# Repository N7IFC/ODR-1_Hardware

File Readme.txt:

This is the hardware repository for the ODR-1 (Open Design Radio - 1) which is a stand-alone "Firmware" defined QRP transceiver.The design goal for the radio is to cover from 1.8MHz (160 meters) up to 50 MHz (6 meters) though it may be able to cover up to 70MHz (4 meters).

The ODR-1 radio consists of the following circuit boards:

1) Display Board
2) Processor Board
3) Oscillator & Mixer Board
4) Amp and tuner board (not released, under design)

Each board hardware revision will have its own directory. When the circuit board layout changes significantly, there is a letter revision. If a minor revision occurs, such as a component value change or a cut and add, then a numeric suffix will be added to the letter revision. this allows older boards to be modified while not impacting the release of new board designs.

All schematic capture and layout is done with stable releases of KiCAD. You are encouraged to support the KiCAD development team as it is an outstanding collection of software.

Hardware - https://github.com/N7IFC/ODR-1_Hardware
Firmware - https://github.com/sylvanwilliams/ODR-1_Firmware

73s!

Bill N7IFC

This work is licensed under the Creative Commons Attribution-ShareAlike 4.0 International License.To view a copy of this license, visit http://creativecommons.org/licenses/by-sa/4.0/ or send a letter to Creative Commons, PO Box 1866, Mountain View, CA 94042, USA.

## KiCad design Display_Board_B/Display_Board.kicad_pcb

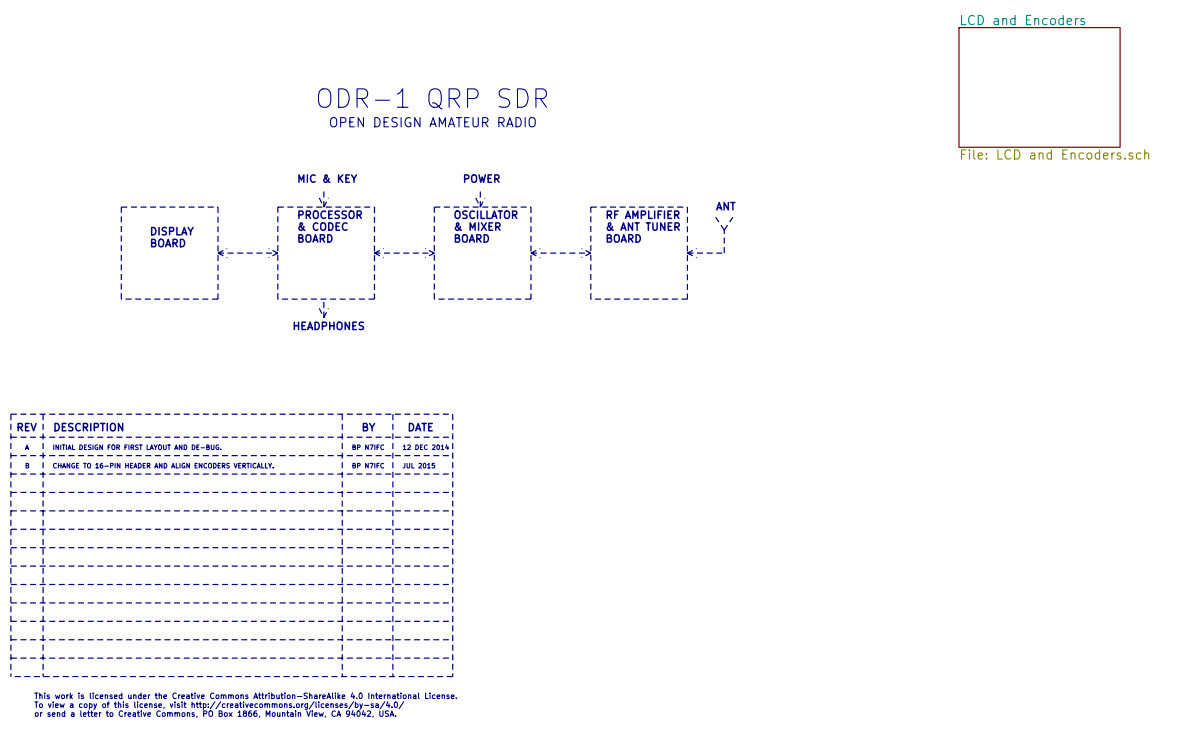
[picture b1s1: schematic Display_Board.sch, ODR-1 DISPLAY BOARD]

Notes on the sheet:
ODR-1 QRP SDR
REV
DESCRIPTION
DATE
INITIAL DESIGN FOR FIRST LAYOUT AND DE-BUG.
BP N7IFC
12 DEC 2014
DISPLAY BOARD
PROCESSOR & CODEC BOARD
OSCILLATOR & MIXER BOARD
RF AMPLIFIER & ANT TUNER BOARD
ANT
MIC & KEY
HEADPHONES
OPEN DESIGN AMATEUR RADIO
POWER
CHANGE TO 16-PIN HEADER AND ALIGN ENCODERS VERTICALLY.
JUL 2015
This work is licensed under the Creative Commons Attribution-ShareAlike 4.0 International License. To view a copy of this license, visit http://creativecommons.org/licenses/by-sa/4.0/ or send a letter to Creative Commons, PO Box 1866, Mountain View, CA 94042, USA.

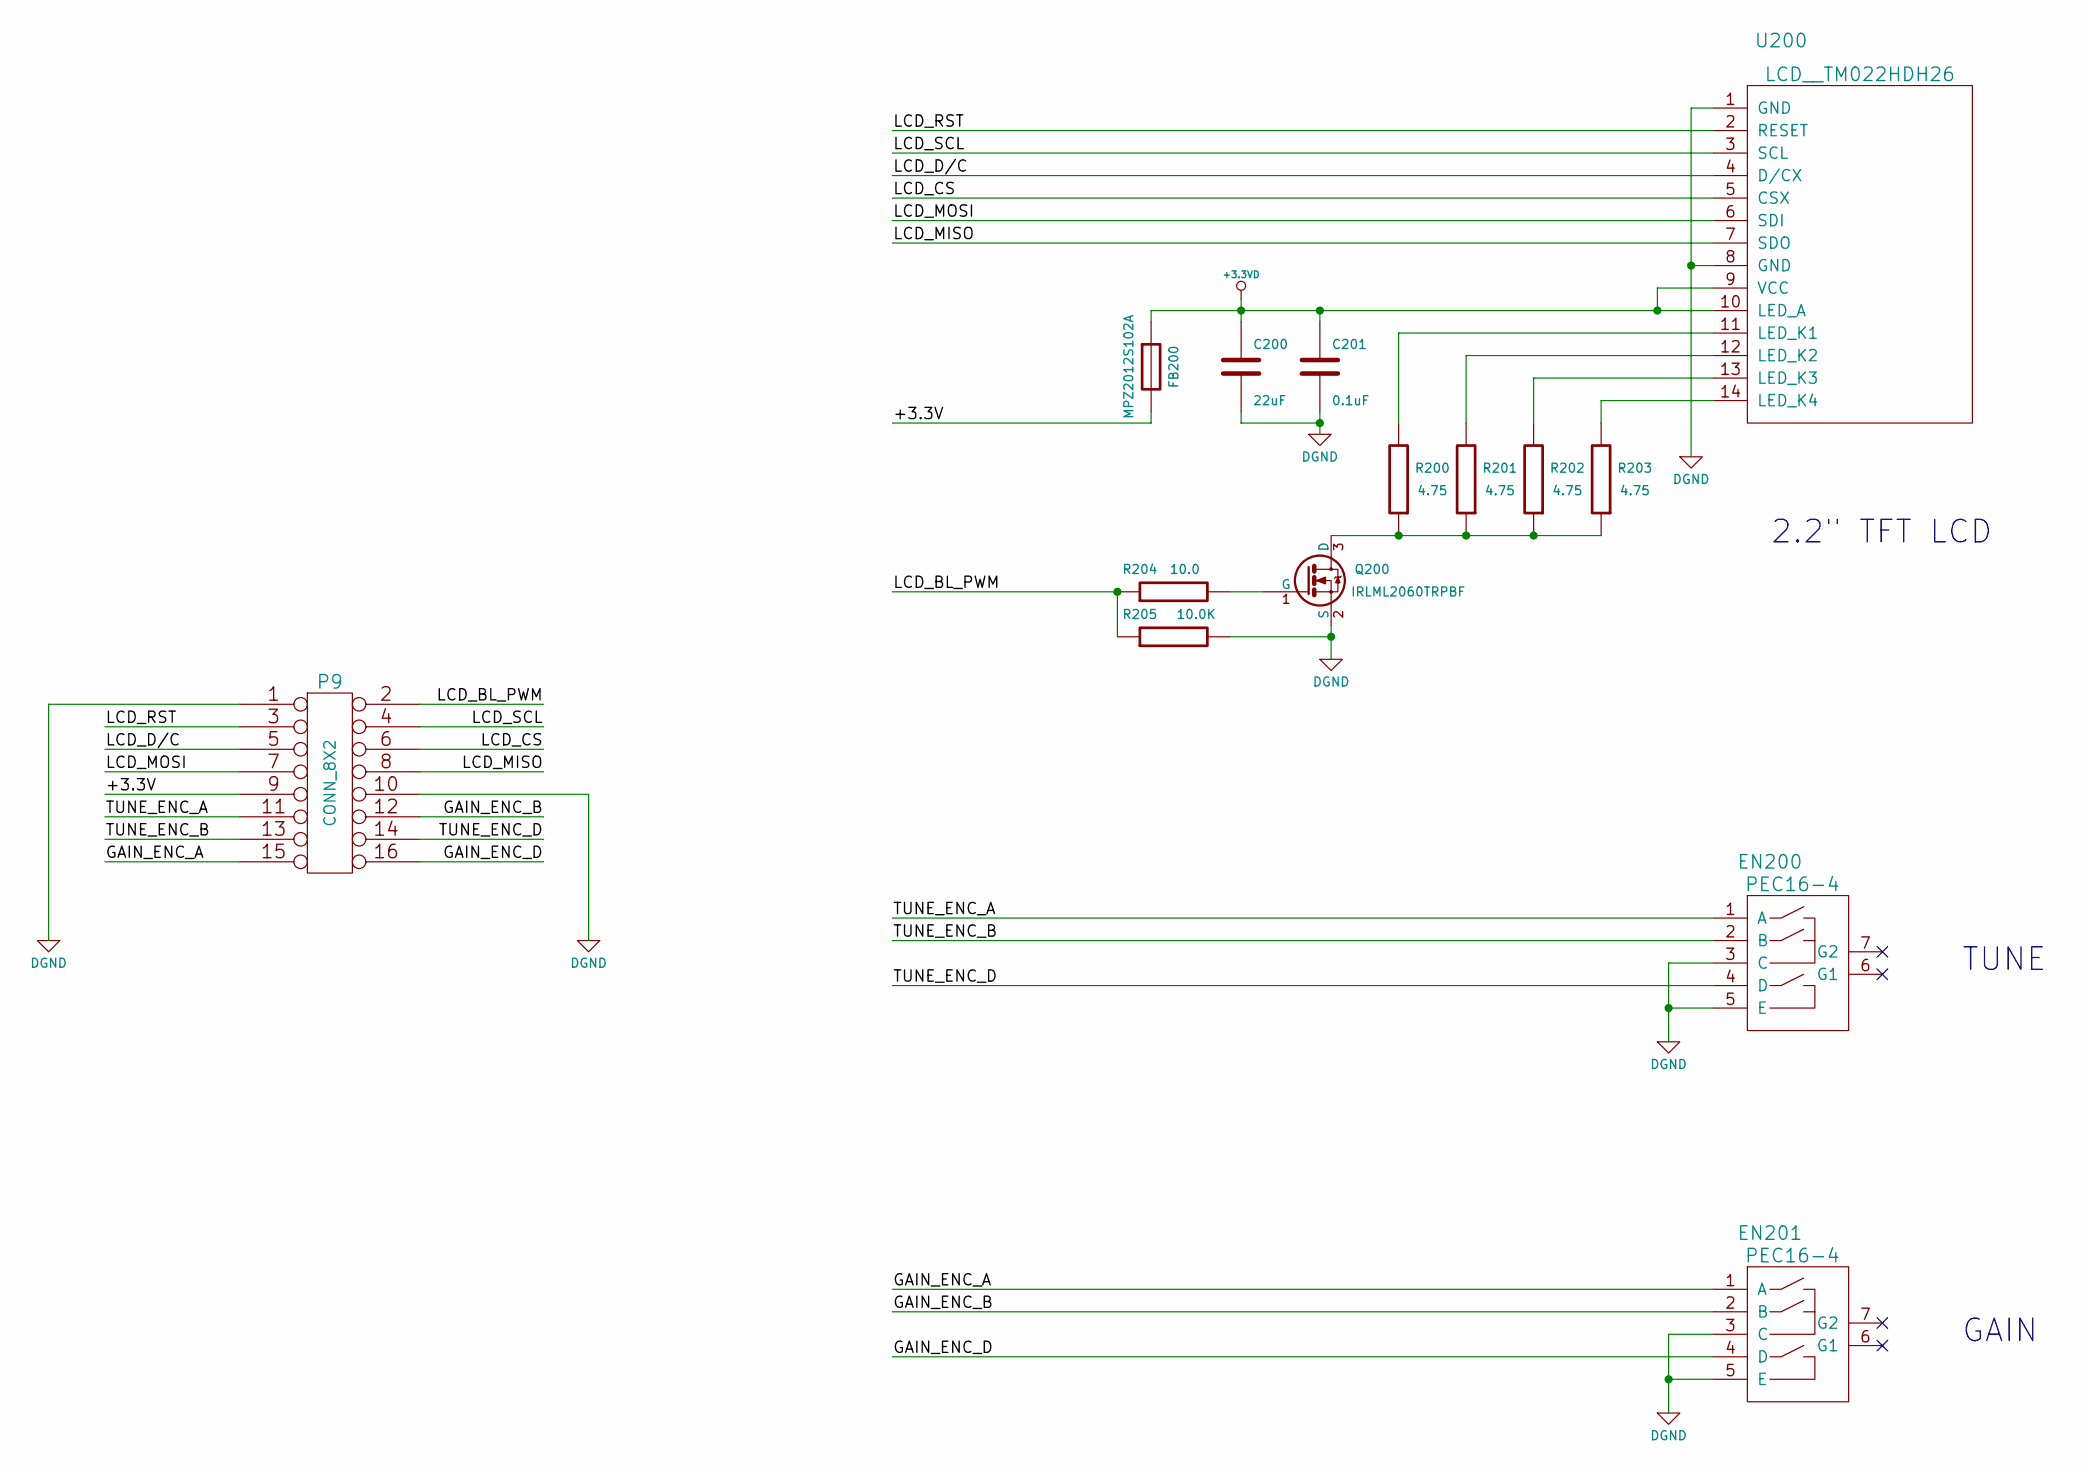
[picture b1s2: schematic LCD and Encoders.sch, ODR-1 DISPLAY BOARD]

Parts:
C200: 22uF; 0805
C201: 0.1uF
EN200, EN201: PEC16-4
FB200: MPZ2012S102A; 0805
P9: CONN_8X2
Q200: IRLML2060TRPBF; SOT-23
R200: 4.75
R201, R202, R203: 4.75; 0805
R204: 10.0; 0805
R205: 10.0K; 0805
U200: LCD__TM022HDH26

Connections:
+3.3VD: C200.1, C201.1, FB200.1, U200.9 (VCC), U200.10 (LED_A)
/LCD and Encoders/+3.3V: FB200.2, P9.9
/LCD and Encoders/GAIN_ENC_A: EN201.1 (A), P9.15
/LCD and Encoders/GAIN_ENC_B: EN201.2 (B), P9.12
/LCD and Encoders/GAIN_ENC_D: EN201.4 (D), P9.16
/LCD and Encoders/LCD_BL_PWM: P9.2, R204.1, R205.1
/LCD and Encoders/LCD_CS: P9.6, U200.5 (CSX)
/LCD and Encoders/LCD_D/C: P9.5, U200.4 (D/CX)
/LCD and Encoders/LCD_MISO: P9.8, U200.7 (SDO)
/LCD and Encoders/LCD_MOSI: P9.7, U200.6 (SDI)
/LCD and Encoders/LCD_RST: P9.3, U200.2 (RESET)
/LCD and Encoders/LCD_SCL: P9.4, U200.3 (SCL)
/LCD and Encoders/TUNE_ENC_A: EN200.1 (A), P9.11
/LCD and Encoders/TUNE_ENC_B: EN200.2 (B), P9.13
/LCD and Encoders/TUNE_ENC_D: EN200.4 (D), P9.14
DGND: C200.2, C201.2, EN200.3 (C), EN200.5 (E), EN201.3 (C), EN201.5 (E), P9.1, P9.10, Q200.2 (S), R205.2, U200.1 (GND), U200.8 (GND)
unnamed: Q200.1 (G), R204.2
unnamed: Q200.3 (D), R200.1, R201.1, R202.1, R203.1
unnamed: R202.2, U200.13 (LED_K3)
unnamed: R200.2, U200.11 (LED_K1)
unnamed: R201.2, U200.12 (LED_K2)
unnamed: R203.2, U200.14 (LED_K4)

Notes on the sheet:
TUNE
GAIN
2.2" TFT LCD

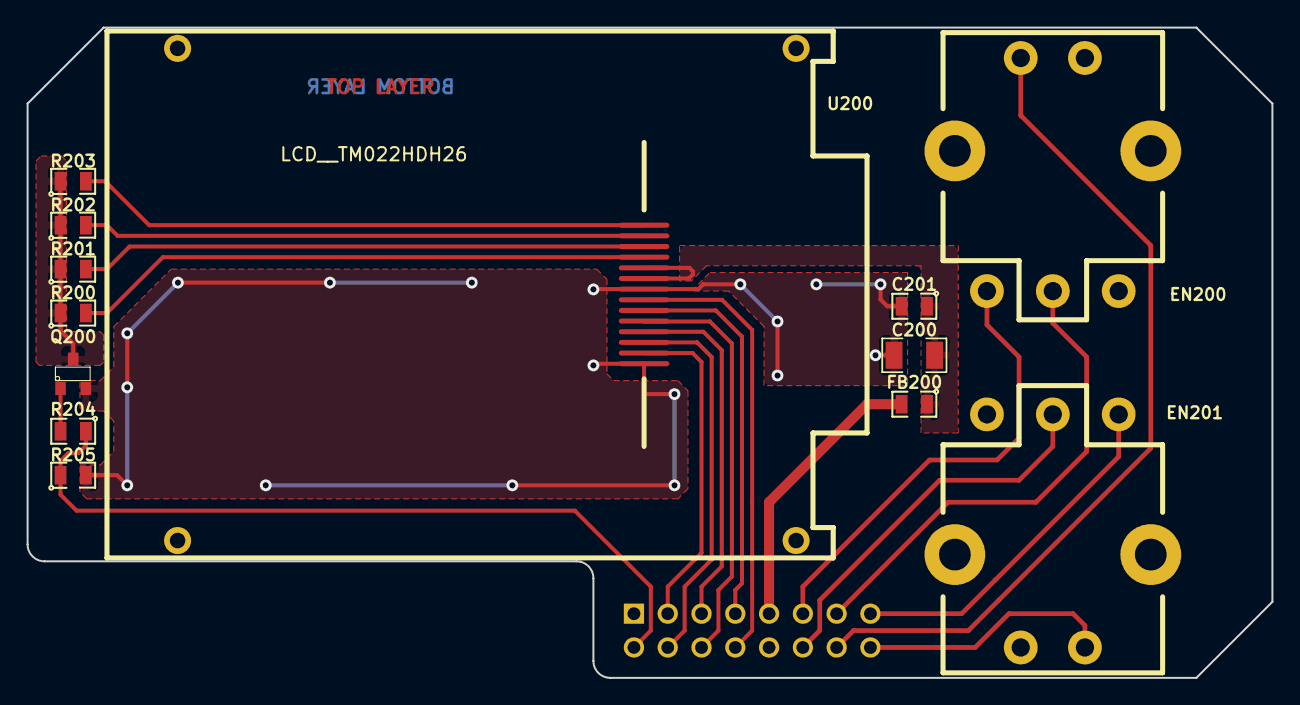
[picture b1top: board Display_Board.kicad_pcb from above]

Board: 2 copper layers, 93.6 x 48.9 mm, 14 parts (1 on the bottom side), 22 nets.

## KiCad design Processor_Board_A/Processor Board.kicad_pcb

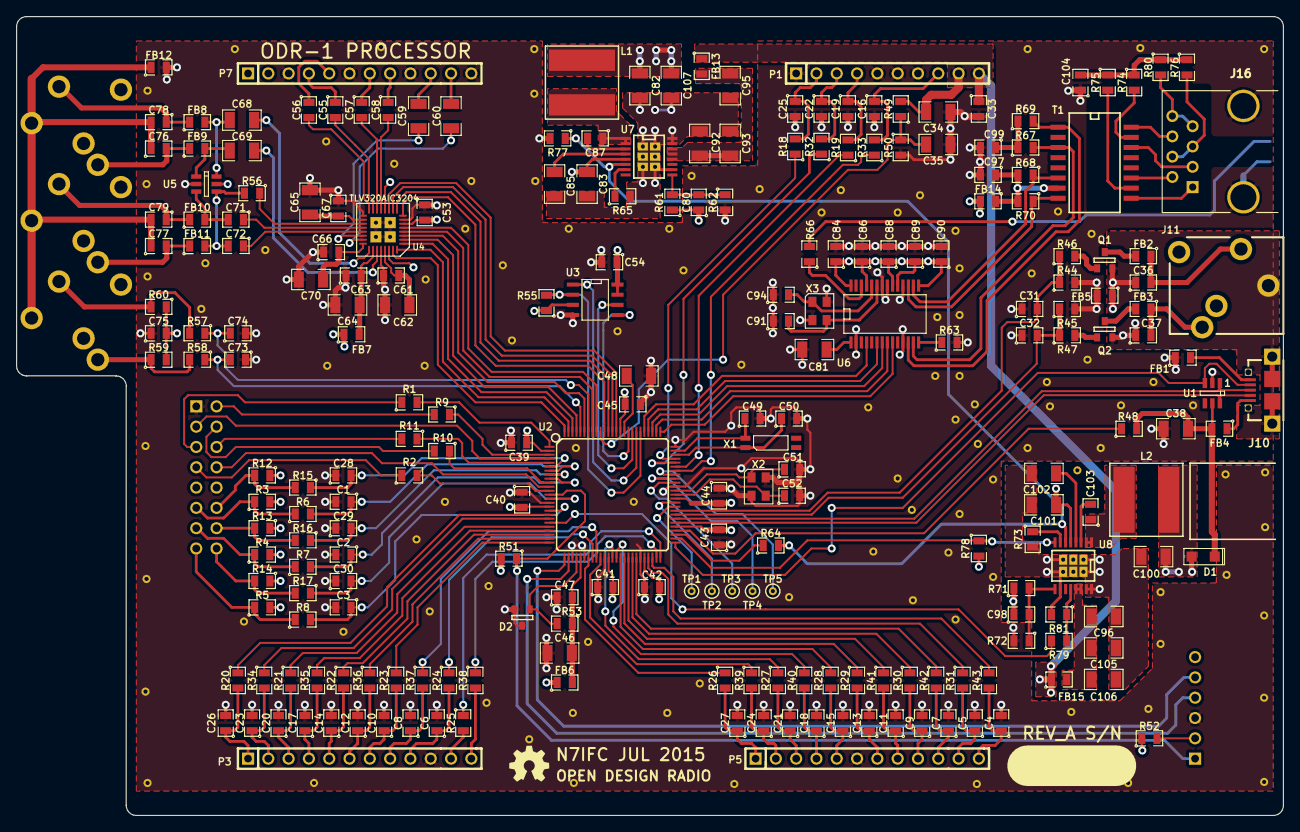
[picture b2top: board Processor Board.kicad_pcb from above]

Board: 4 copper layers, 158.5 x 99.9 mm, 338 parts (0 on the bottom side), 205 nets.

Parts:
C1, C2, C3, C4, C5, C6, C7, C8, C9, C10, C11, C12, C13, C14, C15, C16, C17, C18, C19, C20, C21, C22, C23, C24, C25, C26, C27, C28, C29, C30, C36, C37, C73, C74, C75: 0.01uF; SM0805-1
C31, C32, C76, C77, C78, C79, C104: 1000pF; SM0805-1
C33, C39, C40, C41, C42, C43, C44, C45, C47, C53, C54, C61, C63, C66, C67, C71, C72, C84, C86, C88, C89, C90, C97, C99: 0.1uF; SM0805-1
C34, C38, C81, C83, C93, C95, C101, C105, C106: 4.7uF; SM1206-1
C35, C59, C60, C92, C96: 1uF; SM1206-1
C46, C48, C62, C65: 10uF; SM1206-1
C49, C50, C80, C98: 15pF; SM0805-1
C51, C52, C91, C94: 6pF; SM0805-1
C55, C56, C57, C58: 0.22uF; SM0805-1
C64, C70, C100: 22uF; SM1206-1
C68, C69, C82, C107: 47uF; SM1206-1
C85, C102: 2.2uF; SM1206-1
C87, C103: 0.47uF; SM0805-1
D1: 1A_30V_SCH; SOD123F
D2: LM4040C25; SOT23-1
D3: GRN; SM_LED_RA
FB1, FB2, FB3, FB4, FB5, FB6, FB7, FB12, FB13, FB15: MPZ2012S102A; SM0805-1
FB8, FB9, FB10, FB11, FB14: MMZ2012R102A; SM0805-1
J9: CONN_8X2; HDR_8x2_RA
J10: USB_MICRO_AB
J11, J13, J14, J15: JACK_5P; AUDIO-5
J16: RJ45_LP_UNS; RJ45-8LP
L1: 10uH; SM2233
L2: 22uH; SM2233
P1: M-10; SIL-10-1
P3, P5, P7: M-12; SIL-12-1
P12: CONN_6; SIL-6_RA
Q1, Q2: IRLML2060TRPBF; SOT23-1
R1, R2, R9, R10, R11, R25, R38, R64: 22.1; SM0805-1
R3, R4, R5, R6, R7, R8, R12, R13, R14, R15, R16, R17, R44, R45, R55, R57, R58, R59, R60, R78: 10.0K; SM0805-1
R18, R19, R20, R21, R22, R23, R24, R26, R27, R28, R29, R30, R31, R32, R33, R34, R35, R36, R37, R39, R40, R41, R42, R43, R48, R53: 220; SM0805-1
R46, R47, R77, R79: 1.00K; SM0805-1
R49: 13.7K; SM0805-1
R50: 1.91K; SM0805-1
R51: 4.75K; SM0805-1
R52: 100; SM0805-1
R56: 2.70K; SM0805-1
R61, R71: 1M; SM0805-1
R62: 432K; SM0805-1
R63: 2.32K; SM0805-1
R65, R73: 40.2K; SM0805-1
R66: 270; SM0805-1
R67, R68, R69, R70: 49.9; SM0805-1
R72: 249K; SM0805-1
R74, R75, R76, R80: 75.0; SM0805-1
R81: 100K; SM0805-1
T1: TRANSFO_ETHER; XFMR_ETH16
TP1, TP2, TP3, TP4, TP5: TP_1; TP_TH
U1, U5: TVS_ARRAY_4CH; SOT23-6L
U2: DSPIC33EP512MU810-I/PF (14mm); TQFP_100_14MM
U3: M95256; SO8N-1
U4: TLV320AIC3204; VQFN32
U6: ENC28J60-I/SS; SSOP28-1
U7: LM43601; PWRPAD16
U8: LM43600; PWRPAD16
X1: 32.768 KHz; CRYSTAL_4L
X2: 12.000 MHz; CRYSTAL_4
X3: 25MHz; CRYSTAL_4
x: x; ViaGND40
x#2, x#3, x#4, x#5, x#6, x#7, x#8, x#9, x#10, x#11, x#12, x#13, x#14, x#15, x#16, x#17, x#18, x#19, x#20, x#21, x#22, x#23, x#24, x#25, x#26, x#27, x#28, x#29, x#30, x#31, x#32, x#33, x#34, x#35, x#36, x#37, x#38, x#39, x#40, x#41, x#42, x#43, x#44, x#45, x#46, x#47, x#48, x#49, x#50, x#51, x#52, x#53, x#54, x#55, x#56, x#57, x#58, x#59, x#60, x#61, x#62, x#63, x#64, x#65, x#66, x#67, x#68, x#69, x#70, x#71, x#72, x#73, x#74, x#75, x#76, x#77, x#78, x#79, x#80, x#81, x#82, x#83, x#84, x#85, x#86, x#87, x#88, x#89, x#90, x#91, x#92, x#93, x#94, x#95, x#96, x#97, x#98, x#99, x#100: x; ViaGND40

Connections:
12V_EN: R33.1, U2.69
+3.3VD: C39.2, C40.2, C41.2, C42.2, C43.2, C44.2, C45.2, C53.2, C54.1, C75.2, C80.1, C82.1, C83.1, C84.1, C86.1, C88.1, C89.1, C90.1, C107.1, FB6.1, FB7.1, FB14.2, J9.9, L1.1, R3.2, R4.2, R5.2, R12.1, R13.1, R14.1, R51.2, R52.1, R55.1, R59.2, R60.1, R61.1, R78.2, U2.2, U2.16, U2.37, U2.46, U2.55, U2.62, U2.86, U3.3, U3.7, U3.8, U4.6, U4.12, U4.30, U5.5, U6.15, U6.19, U6.20, U6.25, U6.28, U7.5
+BATT: C33.1, C34.1, FB13.1, FB15.1, P1.9, P1.10, R49.2
/Codec/RX_I+: C55.1, P7.4
/Codec/RX_I-: C56.1, P7.5
/Codec/RX_Q+: C57.1, P7.7
/Codec/RX_Q-: C58.1, P7.8
/Codec/TX_I: C59.1, P7.10
/Codec/TX_Q: C60.1, P7.11
/Processor//MCLR: P12.1, R51.1, U2.13
/Processor/ICSPCLK: P12.5, U2.26
/Processor/ICSPDAT: P12.4, U2.27
AMP-BD01: R32.1, U2.71
AMP-BD02: R19.1, U2.70
AMP-BD03: R34.1, U2.19
AMP-BD04: R21.1, U2.21
AMP-BD05: R35.1, U2.22
AMP-BD06: R22.1, U2.23
AMP-BD07: R36.1, U2.24
AMP-BD08: R23.1, U2.25
AMP-BD09: R37.1, U2.34
AMP-BD10: R24.1, U2.33
AMP-BD11: R26.1, U2.32
AMP-BD12: R39.1, U2.35
AMP-BD13: R27.1, U2.38
AMP-BD14: R40.1, U2.39
AMP-BD15: R28.1, U2.40
ATT_S0: R41.1, U2.42
ATT_S1: R29.1, U2.41
AUX_OUT: C31.2, R44.1, R46.1, U2.59
BATT_V: C35.1, R49.1, R50.1, U2.91
BPF_CS0: R30.1, U2.43
BPF_CS1: R43.1, U2.48
BPF_S0: R31.1, U2.47
BPF_S1: R42.1, U2.44
CODEC_INT1: U2.99, U4.32
CODEC_RST: U2.100, U4.31
COFS-WCLK: U2.95, U4.3
CSCK-BCLK: U2.97, U4.2
CSDI-DOUT: U2.92, U4.5
CSDO-DIN: U2.93, U4.4
GAIN_ENC_A: C3.1, R8.2, U2.17
GAIN_ENC_B: C28.2, R15.1, U2.6
GAIN_ENC_D: C30.2, R17.1, U2.14
GND: C1.2, C2.2, C3.2, C4.2, C5.2, C6.2, C7.2, C8.2, C9.2, C10.2, C11.2, C12.2, C13.2, C14.2, C15.2, C16.2, C17.2, C18.2, C19.2, C20.2, C21.2, C22.2, C23.2, C24.2, C25.2, C26.2, C27.2, C28.1, C29.1, C30.1, C31.1, C32.1, C33.2, C34.2, C35.2, C38.1, C39.1, C40.1, C41.1, C42.1, C43.1, C44.1, C45.1, C46.1, C47.1, C48.1, C49.2, C50.2, C51.2, C52.2, C53.1, C54.2, C61.1, C62.1, C63.1, C64.1, C65.1, C66.1, C67.1, C70.1, C73.1, C74.2, C75.1, C81.2, C82.2, C83.2, C84.2, C85.2, C86.2, C88.2, C89.2, C90.2, C91.1, C92.2, C93.2, C94.1, C95.2, C96.2, C97.2, C99.2, C100.2, C101.2, C102.2, C104.1, C105.2, C106.2, C107.2, D2.2, D2.3, D3.2, FB1.1, FB5.2, FB12.2, J9.1, J9.10, J16.9, J16.10, P1.1, P1.5, P1.6, P1.7, P3.10, P5.6, P7.3, P7.6, P7.9, P7.12, P12.3, R44.2, R45.2, R50.2, R62.2, R63.2, R65.2, R72.2, R73.2, R77.2, R81.2, U1.2, U2.15, U2.28, U2.31, U2.36, U2.45, U2.65, U2.75, U3.4, U4.7, U4.17, U4.28, U4.33, U5.2, U6.2, U6.11, U6.18, U6.21, U6.22, U7.10, U7.15, U7.16, U7.17, U8.10, U8.15, U8.16, U8.17, X2.2, X2.4, X3.2, X3.4, x.1, x#2.1, x#3.1, x#4.1, x#5.1, x#6.1, x#7.1, x#8.1, x#9.1, x#10.1, x#11.1, x#12.1, x#13.1, x#14.1, x#15.1, x#16.1, x#17.1, x#18.1, x#19.1, x#20.1, x#21.1, x#22.1, x#23.1, x#24.1, x#25.1, x#26.1, x#27.1, x#28.1, x#29.1, x#30.1, x#31.1, x#32.1, x#33.1, x#34.1, x#35.1, x#36.1, x#37.1, x#38.1, x#39.1, x#40.1, x#41.1, x#42.1, x#43.1, x#44.1, x#45.1, x#46.1, x#47.1, x#48.1, x#49.1, x#50.1, x#51.1, x#52.1, x#53.1, x#54.1, x#55.1, x#56.1, x#57.1, x#58.1, x#59.1, x#60.1, x#61.1, x#62.1, x#63.1, x#64.1, x#65.1, x#66.1, x#67.1, x#68.1, x#69.1, x#70.1, x#71.1, x#72.1, x#73.1, x#74.1, x#75.1, x#76.1, x#77.1, x#78.1, x#79.1, x#80.1, x#81.1, x#82.1, x#83.1, x#84.1, x#85.1, x#86.1, x#87.1, x#88.1, x#89.1, x#90.1, x#91.1, x#92.1, x#93.1, x#94.1, x#95.1, x#96.1, x#97.1, x#98.1, x#99.1, x#100.1
INT3: U2.80, U6.4
KEY_DOT: C74.1, R57.1, U2.94
KEY_DSH: C73.2, R58.1, U2.96
LCD_BL_PWM: R9.1, U2.3
LCD_CS: R11.1, U2.5
LCD_D-C: R1.2, U2.1
LCD_MISO: J9.8, U2.11
LCD_MOSI: R2.2, U2.12
LCD_RST: J9.3, U2.4
LCD_SCL: R10.1, U2.10
MISO1: U2.87, U4.11
MISO3: U2.79, U6.6
MISO4: R55.2, U2.81, U3.2
MOSI1: U2.88, U4.10
MOSI3: U2.78, U6.7
MOSI4: U2.84, U3.5
unnamed: C6.1, P3.9, R24.2
unnamed: C8.1, P3.8, R37.2
unnamed: C10.1, P3.7, R23.2
unnamed: C12.1, P3.6, R36.2
unnamed: C14.1, P3.5, R22.2
unnamed: C17.1, P3.4, R35.2
unnamed: C20.1, P3.3, R21.2
unnamed: P3.11, R25.2
unnamed: P3.12, R38.2
unnamed: C26.1, P3.1, R20.2
unnamed: C23.1, P3.2, R34.2
unnamed: J9.4, R10.2
unnamed: J9.6, R11.2
unnamed: C5.1, P5.11, R31.2
unnamed: C7.1, P5.10, R42.2
unnamed: C11.1, P5.8, R41.2
unnamed: C13.1, P5.7, R29.2
unnamed: C15.1, P5.5, R28.2
unnamed: C18.1, P5.4, R40.2
unnamed: C21.1, P5.3, R27.2
unnamed: J9.7, R2.1
unnamed: J9.5, R1.1
unnamed: J9.2, R9.2
unnamed: C24.1, P5.2, R39.2
unnamed: C27.1, P5.1, R26.2
unnamed: C9.1, P5.9, R30.2
unnamed: C4.1, P5.12, R43.2
unnamed: C25.1, P1.2, R18.2
unnamed: C16.1, P1.8, R33.2
unnamed: FB4.1, J10.1
unnamed: C38.2, D1.2, FB4.2, R48.2, U1.5
unnamed: J9.15, R5.1, R8.1
unnamed: J9.12, R12.2, R15.2
unnamed: J9.14, R13.2, R16.2
unnamed: J9.16, R14.2, R17.2
unnamed: C22.1, P1.3, R32.2
unnamed: C19.1, P1.4, R19.2
unnamed: FB1.2, J10.5
unnamed: J9.11, R3.1, R6.1
unnamed: J9.13, R4.1, R7.1
unnamed: C36.1, C37.1, FB5.1, J10.6, J10.7, J10.8, J10.9, J10.10, J10.11, J11.1, Q1.2, Q2.2
unnamed: Q2.1, R47.2
unnamed: FB3.2, Q2.3
unnamed: C37.2, FB3.1, J11.2
unnamed: C36.2, FB2.1, J11.5
unnamed: FB2.2, Q1.3
unnamed: Q1.1, R46.2
unnamed: D2.1, R53.2, U2.29
unnamed: C48.2, U2.85
unnamed: TP3.1, U2.66
unnamed: TP4.1, U2.67
unnamed: TP2.1, U2.61
unnamed: TP1.1, U2.60
unnamed: TP5.1, U2.68
unnamed: C52.1, U2.63, X2.3
unnamed: C51.1, U2.64, X2.1
unnamed: C46.2, C47.2, FB6.2, R53.1, U2.30
unnamed: P12.2, R52.2
unnamed: C50.1, U2.73, X1.1
unnamed: C49.1, U2.74, X1.4
unnamed: J15.5, R57.2, R60.2
unnamed: J15.2, R58.2, R59.1
unnamed: C68.1, U4.25
unnamed: C69.1, U4.27
unnamed: C71.1, U4.20
unnamed: C79.1, FB10.1, J14.5
unnamed: C77.2, FB11.1, J14.2
unnamed: C76.1, C77.1, C78.2, C79.2, FB12.1, J13.1, J14.1, J15.1
unnamed: C78.1, FB8.1, J13.5
unnamed: C76.2, FB9.1, J13.2
unnamed: C71.2, FB10.2, U5.3
unnamed: C72.2, FB11.2, R56.2, U5.4
unnamed: C69.2, FB9.2, U5.1
unnamed: C68.2, FB8.2, U5.6
unnamed: C65.2, C67.2, U4.18
unnamed: C66.2, C70.2, U4.24
unnamed: C72.1, U4.21
unnamed: R56.1, U4.19
unnamed: C61.2, C62.2, U4.29
unnamed: C63.2, C64.2, FB7.2, U4.26
unnamed: C57.2, U4.14
unnamed: C56.2, U4.16
unnamed: C55.2, U4.15
unnamed: C58.2, U4.13
unnamed: C60.2, U4.23
unnamed: C59.2, U4.22
unnamed: D3.1, R66.2
unnamed: C91.2, U6.23, X3.3
unnamed: J16.2, T1.11
unnamed: J16.4, J16.5, R76.2
unnamed: J16.1, T1.9
unnamed: J16.7, J16.8, R80.2
unnamed: C87.2, U7.3
unnamed: R65.1, U7.7
unnamed: C92.1, C93.1, C95.1, FB13.2, U7.12, U7.13, U7.14
unnamed: R79.2, R81.1, U8.12
unnamed: C94.2, U6.24, X3.1
unnamed: R75.2, T1.10
unnamed: R63.1, U6.14
unnamed: R66.1, U6.26
unnamed: C81.1, U6.1
unnamed: J16.6, T1.16
unnamed: J16.3, T1.14
unnamed: C102.1, U8.4
unnamed: C98.2, R71.2, R72.1, U8.9
unnamed: C85.1, U7.4
unnamed: R64.2, R77.1, U7.6, U8.6
unnamed: C80.2, R61.2, R62.1, U7.9
unnamed: R73.1, U8.7
unnamed: C96.1, C105.1, C106.1, FB15.2, U8.13, U8.14
unnamed: C103.2, U8.3
unnamed: C97.1, FB14.1, R68.2, R70.2, T1.7
unnamed: C99.1, R67.1, R69.1
unnamed: R68.1, T1.6, U6.16
unnamed: R69.2, T1.1, U6.12
unnamed: R67.2, T1.3, U6.13
unnamed: R70.1, T1.8, U6.17
unnamed: R74.2, T1.15
unnamed: C104.2, R74.1, R75.1, R76.1, R80.1
unnamed: C103.1, L2.2, U8.1, U8.2
unnamed: C87.1, L1.2, U7.1, U7.2
OSC_TMP: R20.1, U2.18
PS_SYNC: R64.1, U2.53
PTT_OUT: C32.2, R45.1, R47.1, U2.58
REFCLKO-MCLK: U2.98, U4.1
RX/TX: R18.1, U2.72
SCK1: U2.90, U4.8
SCK3: U2.77, U6.8
SCK4: U2.83, U3.6
SCL2: R25.1, U2.50
SDA2: R38.1, U2.49
SS1: U2.89, U4.9
SS3: U2.76, U6.9
SS4: U2.82, U3.1
TUNE_ENC_A: C1.1, R6.2, U2.7
TUNE_ENC_B: C2.1, R7.2, U2.9
TUNE_ENC_D: C29.2, R16.1, U2.8
USB_5V: C98.1, C100.1, C101.1, D1.1, L2.1, R71.1, U8.5
USB_D+: J10.3, U1.1, U2.57
USB_D-: J10.2, U1.6, U2.56
USB_FLAG: R78.1, U2.52, U8.8
USB_ID: J10.4, U1.3, U2.51
USB_VBUS: R48.1, U2.54
USB_VBUSON: R79.1, U2.20

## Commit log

2015-08-01 Update library list
2015-08-01 Remove Special Lib and add layout pdf files
2015-08-02 Add Creative Commons License CC BY-SA 4.0
2015-08-09 Add drawing Directory
2015-08-09 Add mechanical drawings
2015-08-14 Update Lens in drawing, spreadsheet print set-up
2015-09-07 add red lines to schematic
2015-10-18 Drawing and red-line updates
2016-01-03 Add Amp and Tuner Board Files
2016-01-04 Add more to schematic
2018-01-13 RF Power Amp Design Updates
    Minor Updates to RF Power Amp Design
2018-01-14 Update Readme
    Update Readme file with links to hardware and firmware projects.
2018-01-14 Update Gitignore
    Add .tmp to gitignore, reprint RF power amp preliminary shematic.
